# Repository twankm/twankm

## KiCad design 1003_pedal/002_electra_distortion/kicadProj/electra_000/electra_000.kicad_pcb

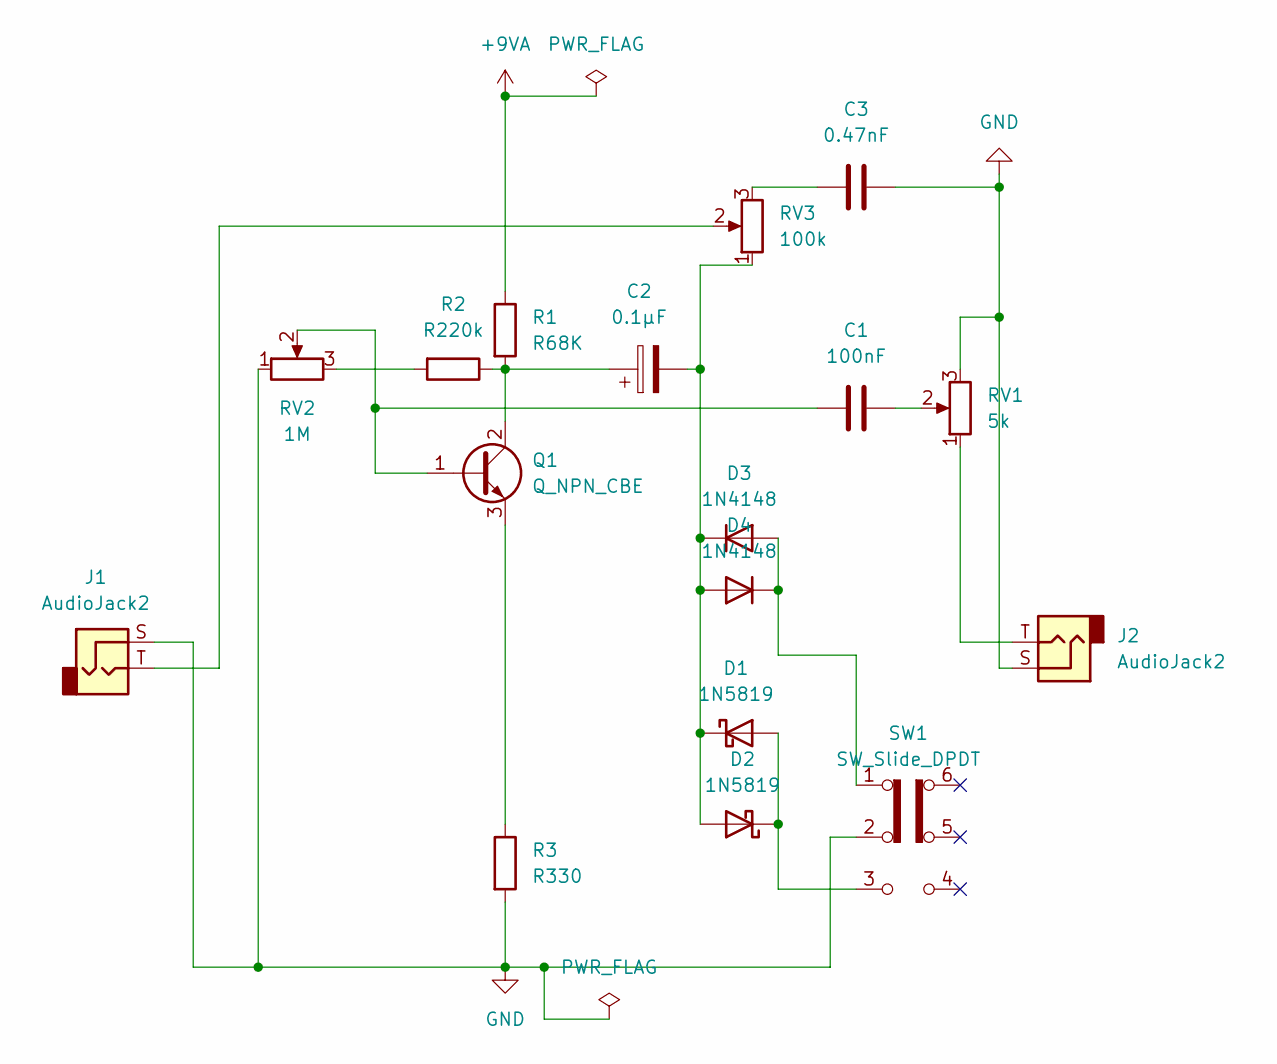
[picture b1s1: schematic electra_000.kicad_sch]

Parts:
C1: 100nF; C_Rect_L10.3mm_W5.0mm_P7.50mm_MKS4
C2: 0.1µF; CP_Radial_D5.0mm_P2.50mm
C3: 0.47nF; C_Disc_D5.0mm_W2.5mm_P5.00mm
D1, D2: 1N5819; D_T-1_P5.08mm_Horizontal
D3, D4: 1N4148; D_T-1_P5.08mm_Horizontal
J1, J2: AudioJack2; PJ612A
Q1: Q_NPN_CBE; TO-92L_INLINE_WIDE
R1: R68K; R_Axial_DIN0204_L3.6mm_D1.6mm_P7.62mm_Horizontal
R2: R220k; R_Axial_DIN0309_L9.0mm_D3.2mm_P12.70mm_Horizontal
R3: R330; R_Axial_DIN0204_L3.6mm_D1.6mm_P7.62mm_Horizontal
RV1: 5k; POT_16MM
RV2: 1M; POT_16MM
RV3: 100k; POT_16MM
SW1: SW_Slide_DPDT; DPDT.LUGS

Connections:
+9VA: R1.1
GND: C3.2, J1.S, J2.S, R3.2, RV1.3, RV2.1, SW1.2 (B)
unnamed: C1.2, RV1.2
unnamed: C3.1, RV3.3
unnamed: D1.2 (A), D2.1 (K), SW1.3 (C)
unnamed: C2.2, D1.1 (K), D2.2 (A), D3.1 (K), D4.2 (A), RV3.1
unnamed: D3.2 (A), D4.1 (K), SW1.1 (A)
unnamed: J1.T, RV3.2
unnamed: J2.T, RV1.1
unnamed: C1.1, Q1.1 (B), RV2.2
unnamed: C2.1, Q1.2 (C), R1.2, R2.1
unnamed: Q1.3 (E), R3.1
unnamed: R2.2, RV2.3

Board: 2 copper layers, 18 parts (0 on the bottom side), 12 nets, no tracks yet.

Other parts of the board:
>NAME: >VALUE; STOMP-SWITCH-3PDT

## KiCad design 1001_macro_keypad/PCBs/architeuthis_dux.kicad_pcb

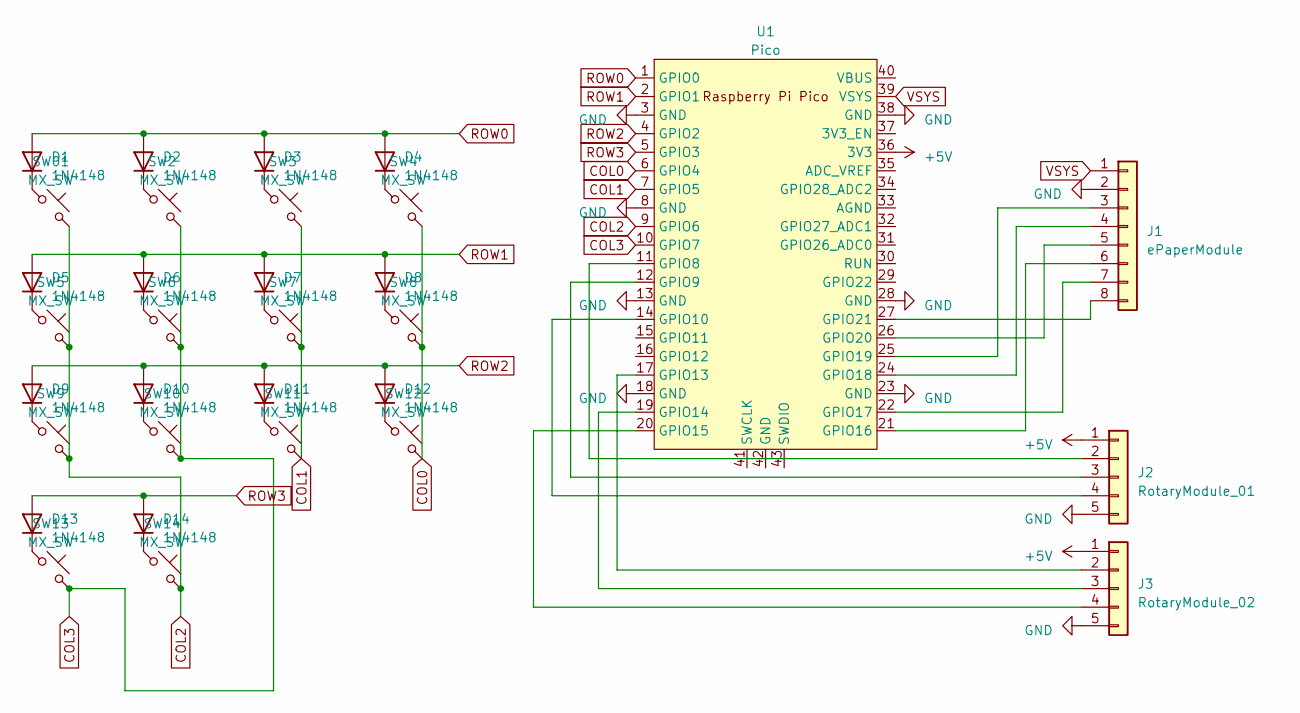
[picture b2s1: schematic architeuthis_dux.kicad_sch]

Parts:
D1, D2, D3, D4, D5, D6, D7, D8, D9, D10, D11, D12, D13, D14: 1N4148; D_DO-35_SOD27_P7.62mm_Horizontal
J1: ePaperModule; PinHeader_2x04_P2.54mm_Vertical
J2: RotaryModule_01; PinHeader_1x05_P2.54mm_Vertical
J3: RotaryModule_02; PinHeader_1x05_P2.54mm_Vertical
SW01, SW2, SW3, SW4, SW5, SW6, SW7, SW8, SW9, SW10, SW11, SW12, SW13, SW14: MX_SW; SW_Cherry_MX_1.00u_PCB
U1: Pico; RPi_Pico_SMD_TH

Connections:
+5V: J2.1 (5V), J3.1, U1.36 (3V3)
COL0: SW4.2, SW8.2, SW12.2, U1.6 (GPIO4)
COL1: SW3.2, SW7.2, SW11.2, U1.7 (GPIO5)
COL2: SW01.2, SW5.2, SW9.2, SW14.2, U1.9 (GPIO6)
COL3: SW2.2, SW6.2, SW10.2, SW13.2, U1.10 (GPIO7)
GND: J1.2 (RES), J2.5 (GND), J3.5, U1.3 (GND), U1.8 (GND), U1.13 (GND), U1.18 (GND), U1.23 (GND), U1.28 (GND), U1.38 (GND)
unnamed: D1.1 (K), SW01.1
unnamed: D2.1 (K), SW2.1
unnamed: D3.1 (K), SW3.1
unnamed: D4.1 (K), SW4.1
unnamed: D5.1 (K), SW5.1
unnamed: D6.1 (K), SW6.1
unnamed: D7.1 (K), SW7.1
unnamed: D8.1 (K), SW8.1
unnamed: D9.1 (K), SW9.1
unnamed: D10.1 (K), SW10.1
unnamed: D11.1 (K), SW11.1
unnamed: D12.1 (K), SW12.1
unnamed: D13.1 (K), SW13.1
unnamed: D14.1 (K), SW14.1
unnamed: J1.4 (CS), U1.24 (GPIO18)
unnamed: J1.3 (D/C), U1.25 (GPIO19)
unnamed: J1.7 (GND), U1.22 (GPIO17)
unnamed: J1.5 (SCL), U1.26 (GPIO20)
unnamed: J1.6 (SDA), U1.21 (GPIO16)
unnamed: J1.8 (VCC), U1.27 (GPIO21)
unnamed: J2.2 (KEY), U1.11 (GPIO8)
unnamed: J2.4 (S1), U1.14 (GPIO10)
unnamed: J2.3 (S2), U1.12 (GPIO9)
unnamed: J3.2, U1.17 (GPIO13)
unnamed: J3.3, U1.19 (GPIO14)
unnamed: J3.4, U1.20 (GPIO15)
ROW0: D1.2 (A), D2.2 (A), D3.2 (A), D4.2 (A), U1.1 (GPIO0)
ROW1: D5.2 (A), D6.2 (A), D7.2 (A), D8.2 (A), U1.2 (GPIO1)
ROW2: D9.2 (A), D10.2 (A), D11.2 (A), D12.2 (A), U1.4 (GPIO2)
ROW3: D13.2 (A), D14.2 (A), U1.5 (GPIO3)
VSYS: J1.1 (BUSY), U1.39 (VSYS)

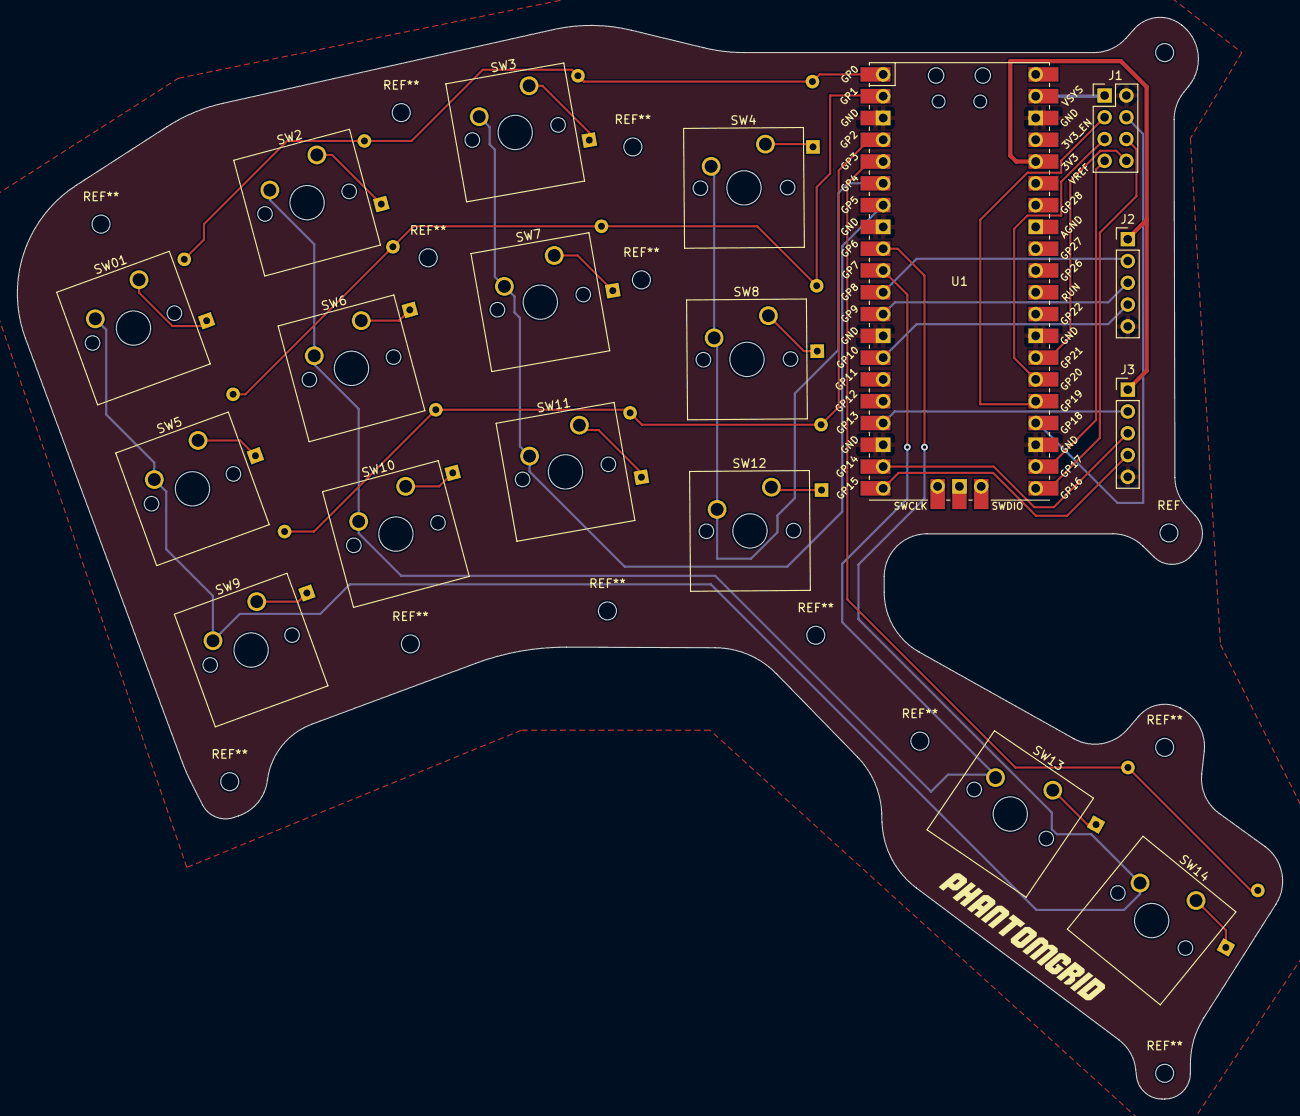
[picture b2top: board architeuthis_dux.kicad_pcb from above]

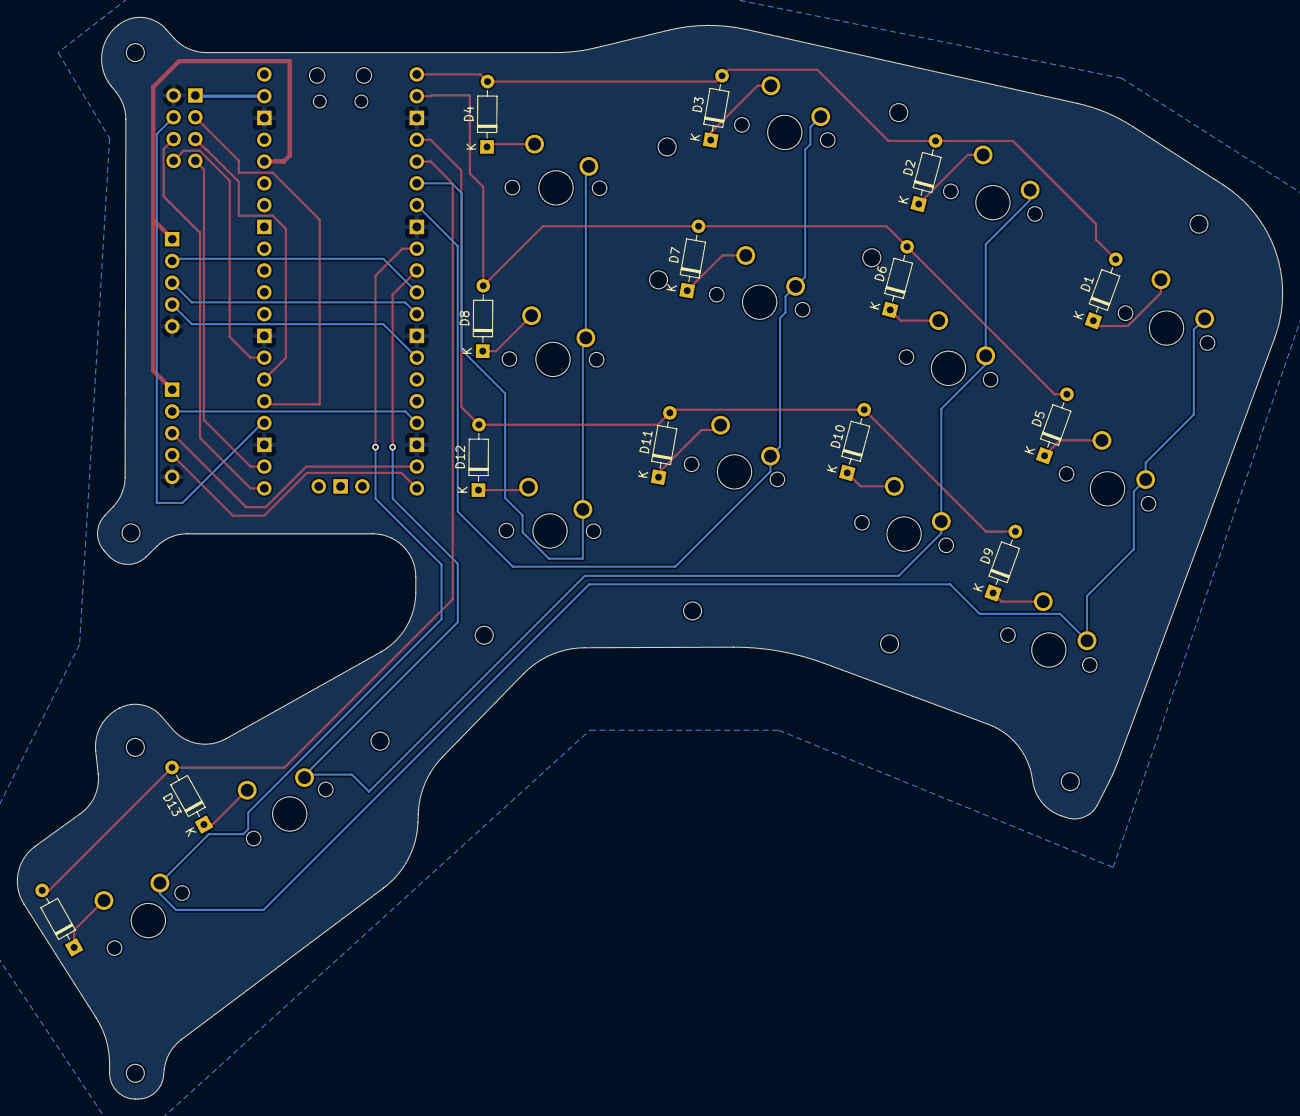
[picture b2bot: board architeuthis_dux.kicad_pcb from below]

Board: 2 copper layers, 147.5 x 126.1 mm, 33 parts (14 on the bottom side), 37 nets.

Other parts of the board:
REF: MountingHole_2.1mm

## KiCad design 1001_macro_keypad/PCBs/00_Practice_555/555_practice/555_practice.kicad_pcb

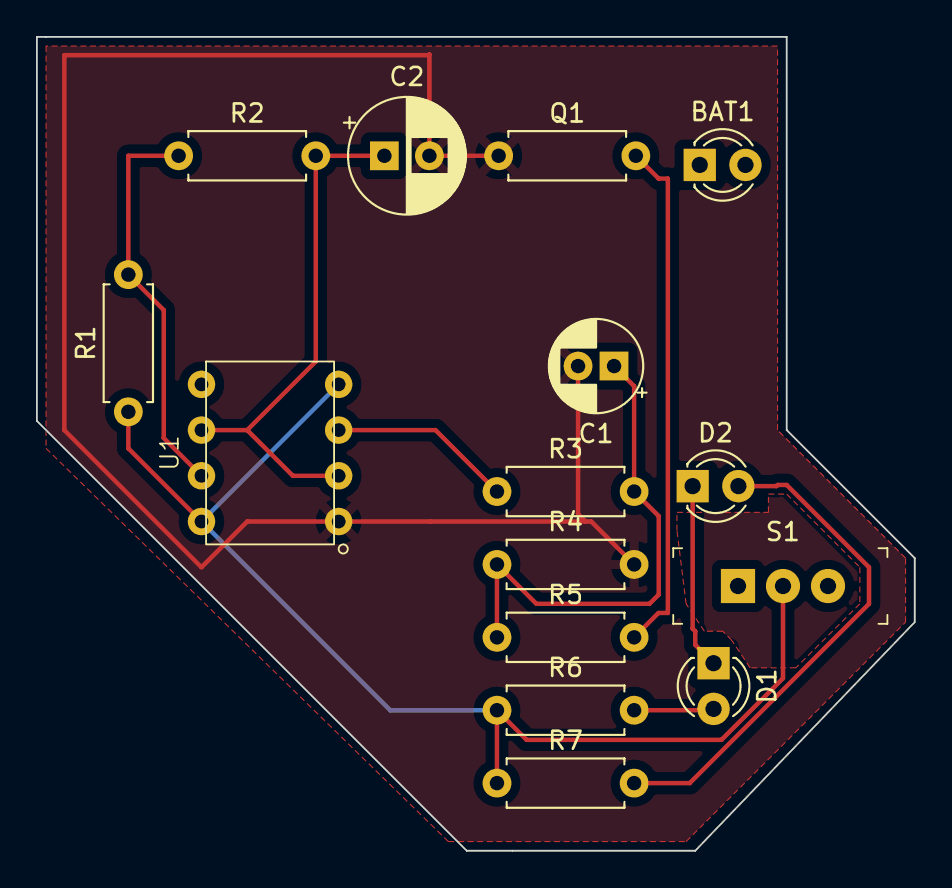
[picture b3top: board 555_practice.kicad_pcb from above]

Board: 2 copper layers, 48.8 x 45.2 mm, 15 parts (0 on the bottom side), 10 nets.

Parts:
BAT1: BS-7; LED_D3.0mm
C1: 100uF; CP_Radial_D5.0mm_P2.00mm
C2: 10uF; CP_Radial_D6.3mm_P2.50mm
D1, D2: RED; LED_D3.0mm
Q1: 2N3904; R_Axial_DIN0207_L6.3mm_D2.5mm_P7.62mm_Horizontal
R1, R3: 22k; R_Axial_DIN0207_L6.3mm_D2.5mm_P7.62mm_Horizontal
R2: 330k; R_Axial_DIN0207_L6.3mm_D2.5mm_P7.62mm_Horizontal
R4, R6, R7: 100k; R_Axial_DIN0207_L6.3mm_D2.5mm_P7.62mm_Horizontal
R5: 10k; R_Axial_DIN0207_L6.3mm_D2.5mm_P7.62mm_Horizontal
S1: EG1218; Switch_Slide_11.6x4mm_EG1218
U1: 7555; ICM7555-PDIP

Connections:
GND: C1.2, C2.2, Q1.1 (E), R4.2, U1.1 (GND)
unnamed: C1.1, R3.2, R4.1, R5.1
unnamed: D1.2 (A), R6.2
unnamed: D1.1 (K), D2.1 (K)
unnamed: D2.2 (A), R7.2
unnamed: Q1.2 (B), R5.2
unnamed: R1.2, R2.1, U1.7 (DIS)
unnamed: R3.1, U1.3 (OUT)
unnamed: C2.1, R2.2, U1.2 (TRIG), U1.6 (THRES)
VCC: R1.1, R6.1, R7.1, S1.2, U1.4 (~RESET), U1.8 (VDD)

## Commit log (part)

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2022-10-25 Create Nordmyra_table_merged.blend
    mordmyra table
2022-10-25 chair drawings
2022-10-26 chair appended
2022-10-27 Added new furnitures
2022-10-28 furniture added
2022-10-30 almost done
2022-11-01 room
2022-11-02 modified shelves, rendered again
2022-11-02 shelves finished, vase added
2022-11-03 ortho added
2022-11-04 room modified
2022-11-05 added bedroom render
2022-11-05 model changed
2022-12-06 Create Tarva_geonodes.blend
    reverted bed's geonode
2023-02-24 Greasepencil test
2023-05-02 폴더정리
2023-05-02 폴더개설
2023-05-08 ergogen 기본 레이아웃 파일
2023-05-09 레이아웃 수정
2023-05-13 pi pico 관련 라이브러리 및 샘플 pcb 설계 파일
2023-05-13 kicad 공부 시작
2023-05-19 연습용 파일들
2023-05-21 Schematic
2023-05-21 pcb modify
2023-05-23 ePaper
2023-05-23 일부수정
2023-05-25 e페이퍼모듈 풋프린트 추가
2023-05-26 배선작업 거의 완료
2023-05-27 pcb 완성, 3d모델 시작
2023-05-27 modeling
2023-05-28 펌웨어 추가, 다이오드 방향 변경 및 재배선
2023-05-29 디스플레이 및 로터리 관련
2023-05-30 epaper 테스트
2023-06-04 배선 변경 및 라이브러리 추가
2023-06-04 설계 픽스 및 모델링 작업 시작
2023-06-05 레퍼런스 리소스 추가 및 하부 케이스 모델링 시작
2023-06-07 모델링 재시작
2023-06-08 모델링 수정
2023-06-09 모델링 거의 완성
2023-06-12 모델링상 설계미스 부분 해결
2023-06-15 모델링수정
2023-06-27 모델링 2차 최종
2023-06-27 stl파일
2023-09-09 car modeling begin
2023-09-12 drawings of bus and modeling
2023-09-13 bus modeling
2023-09-13 bus side
2025-02-25 lumia vehicles
2025-02-26 bus updated to mesh, glsl
2025-03-04 bus update
2025-03-10 references
2025-03-12 keypad retrying
2025-03-14 redesign
2025-03-17 cap modeling
2025-03-17 cap holes
2025-03-18 finalize
2025-03-19 order complete
2025-03-26 car ai test
2025-03-30 keypad firmware
2025-03-31 pyqt test
2025-04-01 키매핑툴 작업
2025-04-02 keymapper function, bottom modeling modificaton start
2025-04-03 keymapper in progress
2025-04-06 keymapping done
2025-04-11 keypad code modified
2025-04-13 keypad code updated
2025-04-18 macro function complete
2025-04-18 deleted unnecessary modules and keymapper updated
2026-06-11 electra distortion start
2026-06-29 kicad project began
2026-06-29 keypad modeling and ui work
2026-06-30 library added
